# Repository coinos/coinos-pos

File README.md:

# Coinos Point of Sale Terminal

This device is intended to be used by retail merchants who want to take Bitcoin payments.

When you enter a sale amount in dollars on the device, it will call the Coinos API to generate an invoice.

Once the invoice is paid, the device lights up and displays a checkmark.

You can scroll through past payments and see if tips were added.

This project was inspired by https://github.com/lnbits/lnpos but the software and hardware is different.

## Parts

- [Xiao Seeed ESP32 C3 Development Board](https://www.aliexpress.com/item/1005006979844970.html)
- [3x4 Matrix Switch Keyboard](https://www.aliexpress.com/item/1005007094229478.html)
- [1.54" 4PIN OLED](https://www.aliexpress.com/item/1005009132302307.html)
- [1800mAH LiPo Battery](https://www.aliexpress.com/item/1005009445456523.html)

Design files for the custom PCB and case are included in this repository.

## Setup

Firmware can be installed with a USB C cable either using Arduino IDE or arduino-cli or visit https://coinos.io/flash to flash from the web. The web flasher's "Flash latest release" button installs the firmware published at https://coinos.io/firmware/manifest.json without touching the device's wifi/token config.

To build and publish a new release to the site, run `./publish.sh` (expects a coinos-ui checkout at `~/coinos-ui` or `$COINOS_UI`), then commit and deploy coinos-ui.

Build locally with:

```
arduino-cli compile -b esp32:esp32:esp32c3:CDCOnBoot=cdc --build-property build.partitions=min_spiffs --build-path=build coinos-pos.ino -u -p /dev/ttyACM0
```

`CDCOnBoot=cdc` routes `Serial` to the XIAO's USB-C port so `cat /dev/ttyACM0` shows the device log.

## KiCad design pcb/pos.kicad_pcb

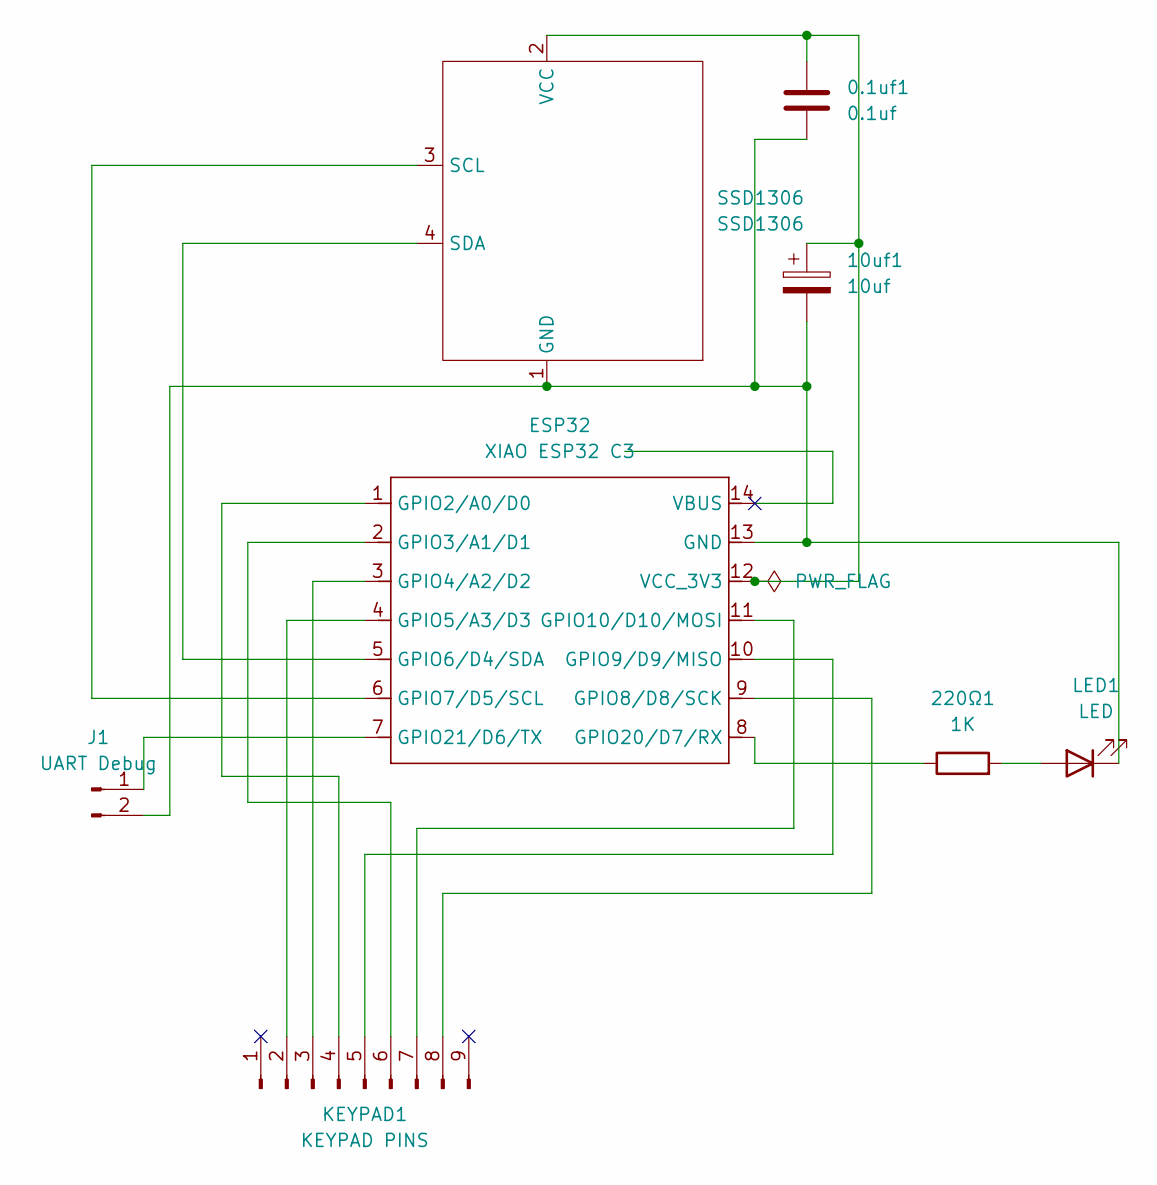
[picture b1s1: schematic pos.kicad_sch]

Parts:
0.1uf1: 0.1uf; C_Disc_D5.0mm_W2.5mm_P2.50mm
10uf1: 10uf; CP_Radial_D5.0mm_P2.00mm
220Ω1: 1K; R_Axial_DIN0207_L6.3mm_D2.5mm_P7.62mm_Horizontal
ESP32: XIAO ESP32 C3; XIAO-ESP32C3-DIP
J1: UART Debug; PinHeader_1x02_P2.54mm_Vertical
KEYPAD1: KEYPAD PINS; Keypad
LED1: LED; LED_D5.0mm
SSD1306: SSD1306; SD1306

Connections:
unnamed: 0.1uf1.2, 10uf1.2, ESP32.13 (GND), J1.2, LED1.1 (K), SSD1306.1 (GND)
unnamed: ESP32.1 (GPIO2/A0/D0), KEYPAD1.4
unnamed: ESP32.2 (GPIO3/A1/D1), KEYPAD1.6
unnamed: ESP32.3 (GPIO4/A2/D2), KEYPAD1.3
unnamed: ESP32.4 (GPIO5/A3/D3), KEYPAD1.2
unnamed: ESP32.5 (GPIO6/D4/SDA), SSD1306.4 (SDA)
unnamed: ESP32.6 (GPIO7/D5/SCL), SSD1306.3 (SCL)
unnamed: ESP32.9 (GPIO8/D8/SCK), KEYPAD1.8
unnamed: ESP32.10 (GPIO9/D9/MISO), KEYPAD1.5
unnamed: ESP32.11 (GPIO10/D10/MOSI), KEYPAD1.7
unnamed: 220Ω1.1, ESP32.8 (GPIO20/D7/RX)
unnamed: ESP32.7 (GPIO21/D6/TX), J1.1
unnamed: 0.1uf1.1, 10uf1.1, ESP32.12 (VCC_3V3), SSD1306.2 (VCC)
unnamed: 220Ω1.2, LED1.2 (A)

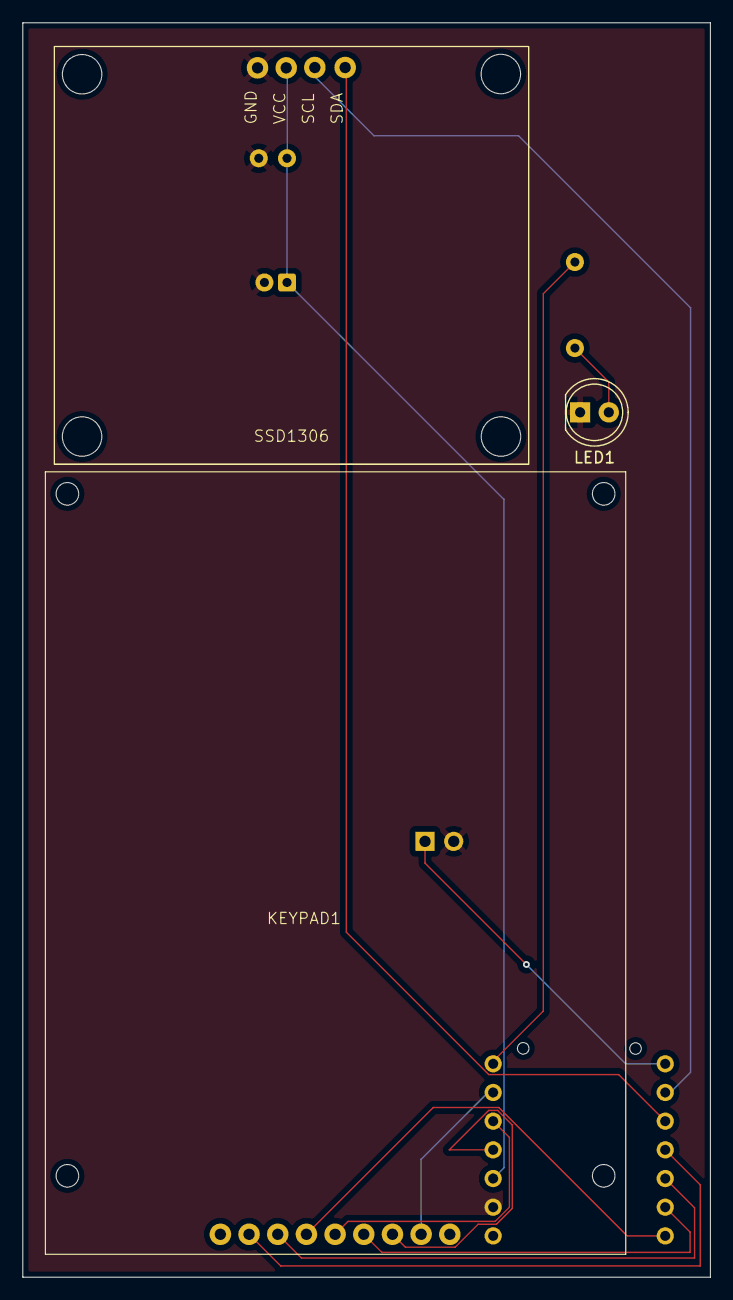
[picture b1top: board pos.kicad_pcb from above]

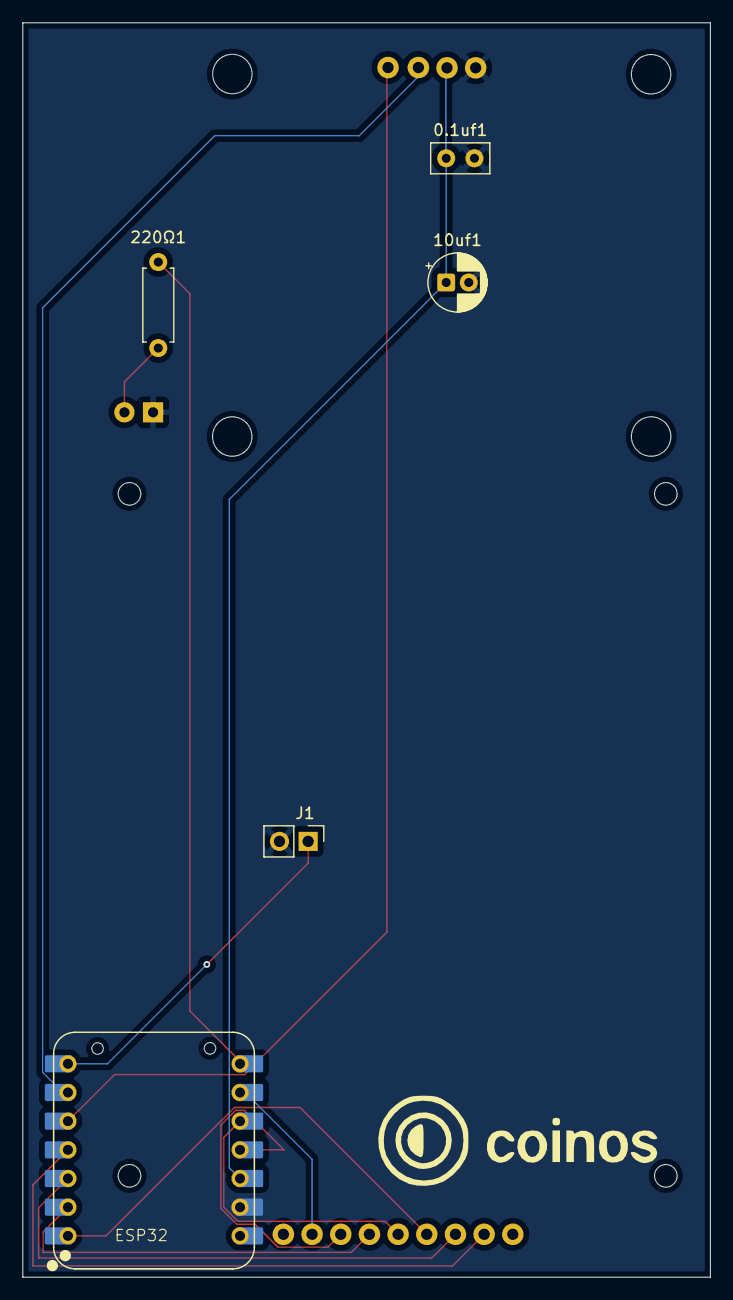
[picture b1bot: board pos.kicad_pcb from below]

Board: 4 copper layers, 60.9 x 111.1 mm, 8 parts (5 on the bottom side), 14 nets.

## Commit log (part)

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2025-10-10 hello world
2025-10-10 readme
2025-10-10 rename main file
2025-10-10 pcb files
2026-03-05 websocket polling and nfc
2026-03-05 fix stale payments
